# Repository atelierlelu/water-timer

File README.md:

# Water timer

CC-BY-4.0. Copyright (c) 2026 Atelier Lelu.

A small device to remind you to water a plant. Battery powered but it lasts years. That's it.

An article about the project is at <https://lelu.uk/water-timer/>.

## How to use

Once assembled, enter setup mode to configure how often it waits before blinks (1, 3 or 7 days) by long pressing the top right button for 1.5 seconds. When you release you can cycle through durations by pressing the centre button - green LEDs will blink once (for 1 day), 3 times (for 3 days) or a long blink for 7 days. It auto saves after 10 seconds.
Once the 1/3/7 days have passed, the device will blink green every minute (twice) to remind you to water the plant. Once watered press the centre button once, green LEDs flash as acknowledgement and that's it.
When the battery is low the red light will flash on button presses of when watering is due - but it should take years before you reach that point.

## In this repository

| Path | What it is |
| --- | --- |
| `enclosure/print/` | STLs to print: back, front, light mask, hook |
| `enclosure/source/` | Matching STEP files, for editing |
| `hardware/` | KiCad project, plus the JLCPCB gerbers, BOM and placement file. The schematic is [hardware/schematic.pdf](hardware/schematic.pdf) |
| `firmware/` | Plant-timer firmware, flash and test tools |
| `docs/` | Documentation |

## Make one

Print the four STLs, order the board, solder the coin-cell holder, flash the firmware, then close the case. The steps, including which jumper to close for a cell-powered timer, are in [docs/build.md](docs/build.md).

Flash before the board goes into the case. From `firmware/`:

```bash
make
make flash
```

Leave the option bytes alone. Programmer wiring and the button and LED behaviour are in [firmware/README.md](firmware/README.md).

Assembly, in order: hook, cell, board on the alignment pins, light mask, front. There are no screws. The picture is [docs/exploded.png](docs/exploded.png).

## License

Three licenses, one per kind of file. See [LICENSE.md](LICENSE.md). Hardware is CERN-OHL-P-2.0, firmware is MIT, and the documents are CC-BY-4.0. The ST files under `firmware/Drivers/` stay BSD-3-Clause.

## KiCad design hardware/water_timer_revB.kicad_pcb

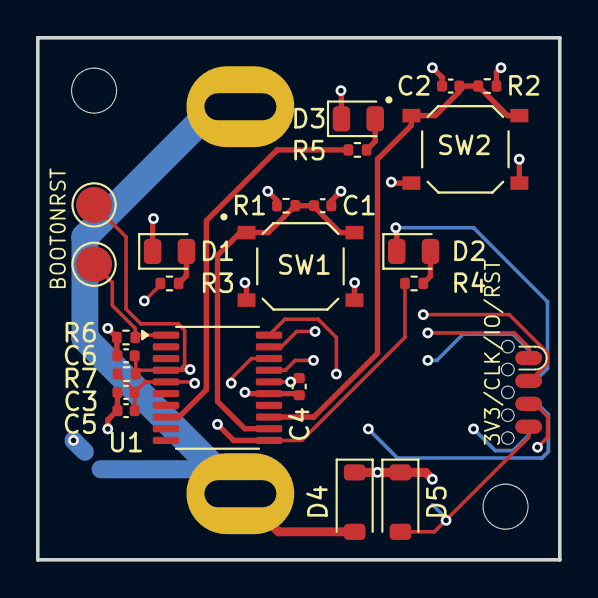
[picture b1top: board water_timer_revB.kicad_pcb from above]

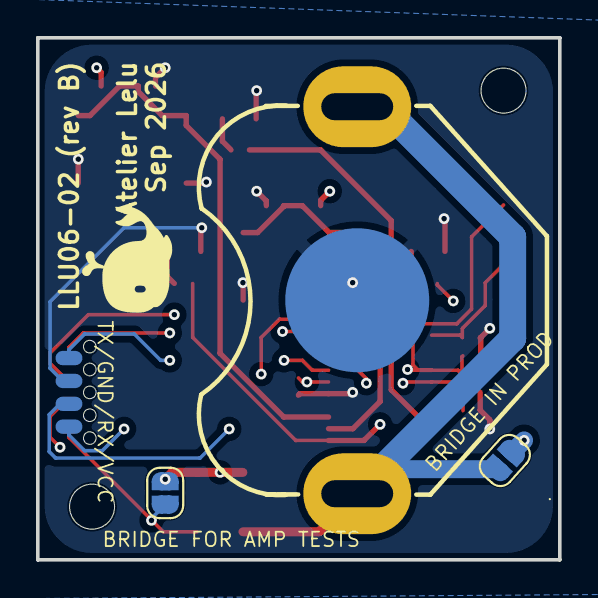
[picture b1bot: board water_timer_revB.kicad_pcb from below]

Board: 4 copper layers, 29.0 x 29.0 mm, 29 parts (3 on the bottom side), 17 nets.

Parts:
C1, C2, C4, C5, C6: 0.1u; C_0402_1005Metric
C3: 10u; C_0402_1005Metric
D1, D2: Green; LED_0805_2012Metric
D3: Red; LED_0805_2012Metric
D4, D5: D_Schottky; D_SOD-123
H1, H2: MountingHole; MountingHole_2.5mm
J2: Conn_02x04_Top_Bottom; SOIC_clipProgSmall
JP1, JP2: SolderJumper_2_Open; SolderJumper-2_P1.3mm_Open_RoundedPad1.0x1.5mm
P1: S2B-PH-SM4-TB; BAT-TH_MY-2032-22
R1, R2, R3, R4, R5, R6, R7: 10k; R_0402_1005Metric
SW1, SW2: SW_Push; TS-1187A-B-A-B SPST switch
TP8, TP11: TestPoint; TestPoint_Pad_D2.0mm
U1: STM32L011F4Px; TSSOP-20_4.4x6.5mm_P0.65mm

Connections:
3V3: D5.2 (A), J2.4, JP2.1 (A)
BUTTON_1: C1.1, R1.2, SW1.1, U1.12 (PA6)
BUTTON_2: C2.1, R2.2, SW2.1, U1.13 (PA7)
GND: C1.2, C2.2, C3.2, C4.2, C5.2, C6.1, D1.1 (K), D2.1 (K), D3.1 (K), J2.7, P1.2, R6.1, SW1.2, SW2.2, U1.15 (VSS)
GREEN: R3.1, R4.1, U1.11 (PA5)
NRST: C6.2, J2.1, R7.1, TP11.1 (1_1), U1.4 (NRST)
unnamed: D1.2 (A), R3.2
unnamed: D2.2 (A), R4.2
unnamed: D3.2 (A), R5.2
PB9/BOOT0: R6.2, TP8.1 (1_1), U1.1 (PB9)
RED: R5.1, U1.8 (PA2)
SWCLK: J2.3, U1.20 (PA14)
SWDIO: J2.2, U1.19 (PA13)
UART2_RX: J2.6, U1.18 (PA10)
UART2_TX: J2.8, U1.17 (PA9)
VBAT: D4.2 (A), JP1.1 (A), P1.1
VCC: C3.1, C4.1, C5.1, D4.1 (K), D5.1 (K), J2.5, JP1.2 (B), JP2.2 (B), R1.1, R2.1, R7.2, U1.5 (VDDA), U1.16 (VDD)

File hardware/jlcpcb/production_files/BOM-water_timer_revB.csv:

Comment,Designator,Footprint,LCSC,Quantity
0.1u,"C1,C2,C4,C5,C6",C_0402_1005Metric,C1525,5
10k,"R1,R2,R3,R4,R5,R6,R7",R_0402_1005Metric,C25744,7
10u,C3,C_0402_1005Metric,C15525,1
D_Schottky,"D4,D5",D_SOD-123,C7420332,2
Green,"D1,D2",LED_0805_2012Metric,C2297,2
Red,D3,LED_0805_2012Metric,C84256,1
STM32L011F4Px,U1,TSSOP-20_4.4x6.5mm_P0.65mm,C503083,1
SW_Push,"SW1,SW2",TS-1187A-B-A-B SPST switch,C318884,2

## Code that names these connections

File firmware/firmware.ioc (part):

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Mcu.Name=STM32L011F(3-4)Px
Mcu.Package=TSSOP20
Mcu.UserName=STM32L011F4Px
PA10.Mode=Asynchronous
PA10.Signal=USART2_RX
PA13.Mode=Serial_Wire
PA13.Signal=SYS_SWDIO
PA14.Mode=Serial_Wire
PA14.Signal=SYS_SWCLK
PA2.GPIOParameters=GPIO_Label
PA2.GPIO_Label=RED
PA2.Signal=GPIO_Output
PA5.GPIOParameters=GPIO_Label
PA5.GPIO_Label=GREEN
PA5.Signal=GPIO_Output
PA6.GPIOParameters=GPIO_Label
PA6.GPIO_Label=BUTTON_1
PA6.Signal=GPIO_Input
PA7.GPIOParameters=GPIO_Label
PA7.GPIO_Label=BUTTON_2
PA7.Signal=GPIO_Input
PA9.Mode=Asynchronous
PA9.Signal=USART2_TX
RCC.HSE_VALUE=8000000
RCC.SYSCLKFreq_VALUE=2097000
board=custom
